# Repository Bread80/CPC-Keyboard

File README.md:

# Keyboard for Amstrad CPC Computers

This project is a keyboard suitable for direct connection to an Amstrad CPC. The PCB uses tactile switches which can easily be labelled with suitable legends for the keytops. The current layout is that of an Amstrad CPC6128, but the key matrix is the same across all machines. The only differences are in the connector types and pinouts.

This board has connectors which are compatible with:
* CPC464 with PCB keyboard (1x20 pin connector)
* CPC464 with membrane keyboard (2x10 pin connectors)
* CPC664 (1x20 pin connector) **Untested**
* CPC6128 (2x10 pin connectors)

Plus machines: I'm not clear whether they use the same keyboard pinout or not. As such I can't say whether this board works with them or not.

Sadly it's not practical to add mounting holes suitable for mounting the keyboard on top of the CPC mainboard.

The repository includes an SVG file with key legend. This is suitable for the open source [Inkscape](https://inkscape.org) software

## BoM

74x Key switches[1]: Alps Apline SKHCBEA010. Mouser no: 688-SKHCBEA010
74x Keytops + Keycaps[2][3]: Alps Alpine SK2AA00090. Mouser: 688-SK2AA00090
'Standard pin header' (2.54mm spacing)[4]
2x Shunts[4]
Connector(s) (to keyboard)[5]
Connector(s) (to CPC)[6]
Cable (keyboard to CPC)[7]
5x Standoffs, short)[8]: 13mm length, M3 x 0.5, 4.5mm OD, female/female. Mouser: M1260-3005-SS
5x Standoffs, long)[8]: 25mm, M3 x 0.5, 4.5mm OD, female/female. Mouser: 761-M1272-3005-SS
10x Screws[8]: M3 x 6mm. Mouser: 534-9191-3
--also-- key legend (printout)[9]

### Notes:
Mouser codes can be used at http://mouser.com
[1] PCB will accept any generic 12mm 'tactile switch'. The specified model allows a keytop + keycap to be attched. This enables a printed key legend to be used. The same design is available engineered for 'operating force' values. In my tests this model had the best feel.
[2] Other colours are available (for the keytops), product codes SK2AA000x0 where x is 6,7,8,9 (NOTE: other digits are different products!).
[3] This product code includes both keycap and keytop. These are also available separately, but the combined pack is slightly cheaper.
Consult the keyswitch data sheet for the full list of available options: https://www.mouser.co.uk/datasheet/2/15/SKHC-1370786.pdf

[4] For configuration jumpers. Source from ebay etc for sensible pricing. If you don't intend to change settings you can solder an offcut of wire instead.
[5] Unless you need to attach multiple machines your best option here is to directly solder wire to the board. Otherwise pin header is probably the most convenient. You'll either need 1x20 or 2x10 depending on the machine, plus 
[6] Options here depend on your machine. The 20-pin inline connect machines will accept 'Dupont' style connectors, pin header etc. The 2x10 matrix connectors are more of a pin. I've successfully used FPC/FFC cable. With some patience this can be persuaded into the connector. These cables only seem to be available in very short lengths but ribbon (etc) cable can be soldered to the other end to run to the keyboard. Obviously some insulation will be helpful on the joins to prevent it shorting against anything (or each other)! You'll need 2x 10-pin cables, 571-FSN-21A-10 is a suitable Mouser product code.
[7] Discreet cables or a length or ribbon cable is up to you. Not every line is connected but using a 20pin or 2x 10-pin ribbon cable saves you having to etsablish which aren't needed. Cable length is up to you but anything too short will make it difficult to position the keyboard where you want it. I'd suggest a /minimum/ of about eight inches (40cm).
[8] I use standoffs as feet to lift to board of the desk and give space for the wiring underneath. You can give the keyboard some 'raking' by using longer ones at the rear. another option is to use a male/female standoff as an extender. The board is engineered for M3 screws/threads. Note: The PCB has three rows of mounting holes but the central row has not proved necessary and I'll remove them if I do an update. Just use the top and bottom rows.
[9] Provided as an SVG suitable for Inkscape) in this here repository. If creating your own key legend, each key needs to be a maximum 10mm x 10mm

## Known Issues

* The keyswitches have a pair of small lugs on the underside. Fitting them would be easier if the board had siutable holes for them. As is it just needs some care to ensure each switch sits flag and true.

## Assembly guide

### Soldering:
* Pin header. Solder the pin header strips for the settings jumpers. Pin header can easily be snapped into short sections as needed.
* Start with the keyswitches. Mount them any way which fits the holes and you'll be okay! Note that there are small lugs on the underside which make them want to sit at an angle. I /strongly/ recommend taking some care to check they are sitting flat and level. My method is to solder a single leg on each, then inspect and rework as needed to level them. Once they're level solder the remaining pins.
* Connectors. Solder your preference of connector(s), or wire, to the rear of the board. The required connectors are as follows:
For a CPC464 with PCB keyboard: connector J1 (1x20 pin)
For a CPC464 with matrix keyboard: connectors J2 and J3 (2 of 1x10 pin)
For a CPC664: connector J4 (1x20 pin)
For a CPC6128: connectors J2 and J3 (2 of 1x10 pin)

### Keycaps:
* Print out the key legend sheet and cut up. Cutting as accurately to the lines as possible will be beneficial. If you have them available, using a cutting board, craft knife, and steel ruler will probably give a better finish than scissors.
* Before assembling the key top + key legend + key cap consult the assembly diagram at the bottom of page three of the datasheet: https://www.mouser.co.uk/datasheet/2/15/SKHC-1370786.pdf Note the recommended orientation of keytop to keycap and plan which way you'll need to assemble things so your legend ends up the correct way around!
* With the keycap (clear plastic piece) face down on the bench, insert the key legend (paper) face down. Then insert the keytop into the keycap, taking note of the corrent orientation with respect to the key legend.
* Attach the keytop/keycaps to the keyswitches.

### Configuration and Connection

All the connectors are orientated in the same way as those on the Amstrad motherboard. I.e. the pin(s) towards the top of rear of the keyboard PCB are those towards the rear of the motherboard PCB and, for the the dual 10-pin connectors, the right-most connector on the keyboard PCB (when viewed from the top) connects to the right-most connector on the motherboard PCB.

Configuration is *only* needed if using the pair of 10-pin connectors to connect to the motherboard. If connecting to a CPC464, short (with a 'shunt') JP2 and the left-most two pins of JP1. If connecting to a CPC6128 short JP3 and the two right-most pins of JP1. Note that when connecting to a CPC464 JP3 should be left open, when connecting to a CPC6128 JP2 should be left open.

## Keyboard legend file(s)

Keyboard legend files are in the 'legend' folder. The following designs/layouts are available. SVG files can be created, edited and printed with the open source Inkscape software. If you create anything new/interesting please contribute it back to the repository.

UK-CPC6128-with-464-colours.svg - Amstrad CPC6128 layout with UK legend using the colour scheme of an original Amstrad CPC464.

## Licence

My aim with this project is to share something potentially useful with the community but I don't want to see my work being exploited for profit.

Therefore, it's okay to have a board manufactured for your own use and sell off the spare boards for an amount to cover your costs and postage. If you want to sell boards, or derivatives, for profit or as part of a business then talk to me first.

## Contact

Website: https://bread80.com
Github: https://github.com/Bread80
Mastodon: https://mstdn.social/@bread80
Twitter: https://twitter.com/bread80com

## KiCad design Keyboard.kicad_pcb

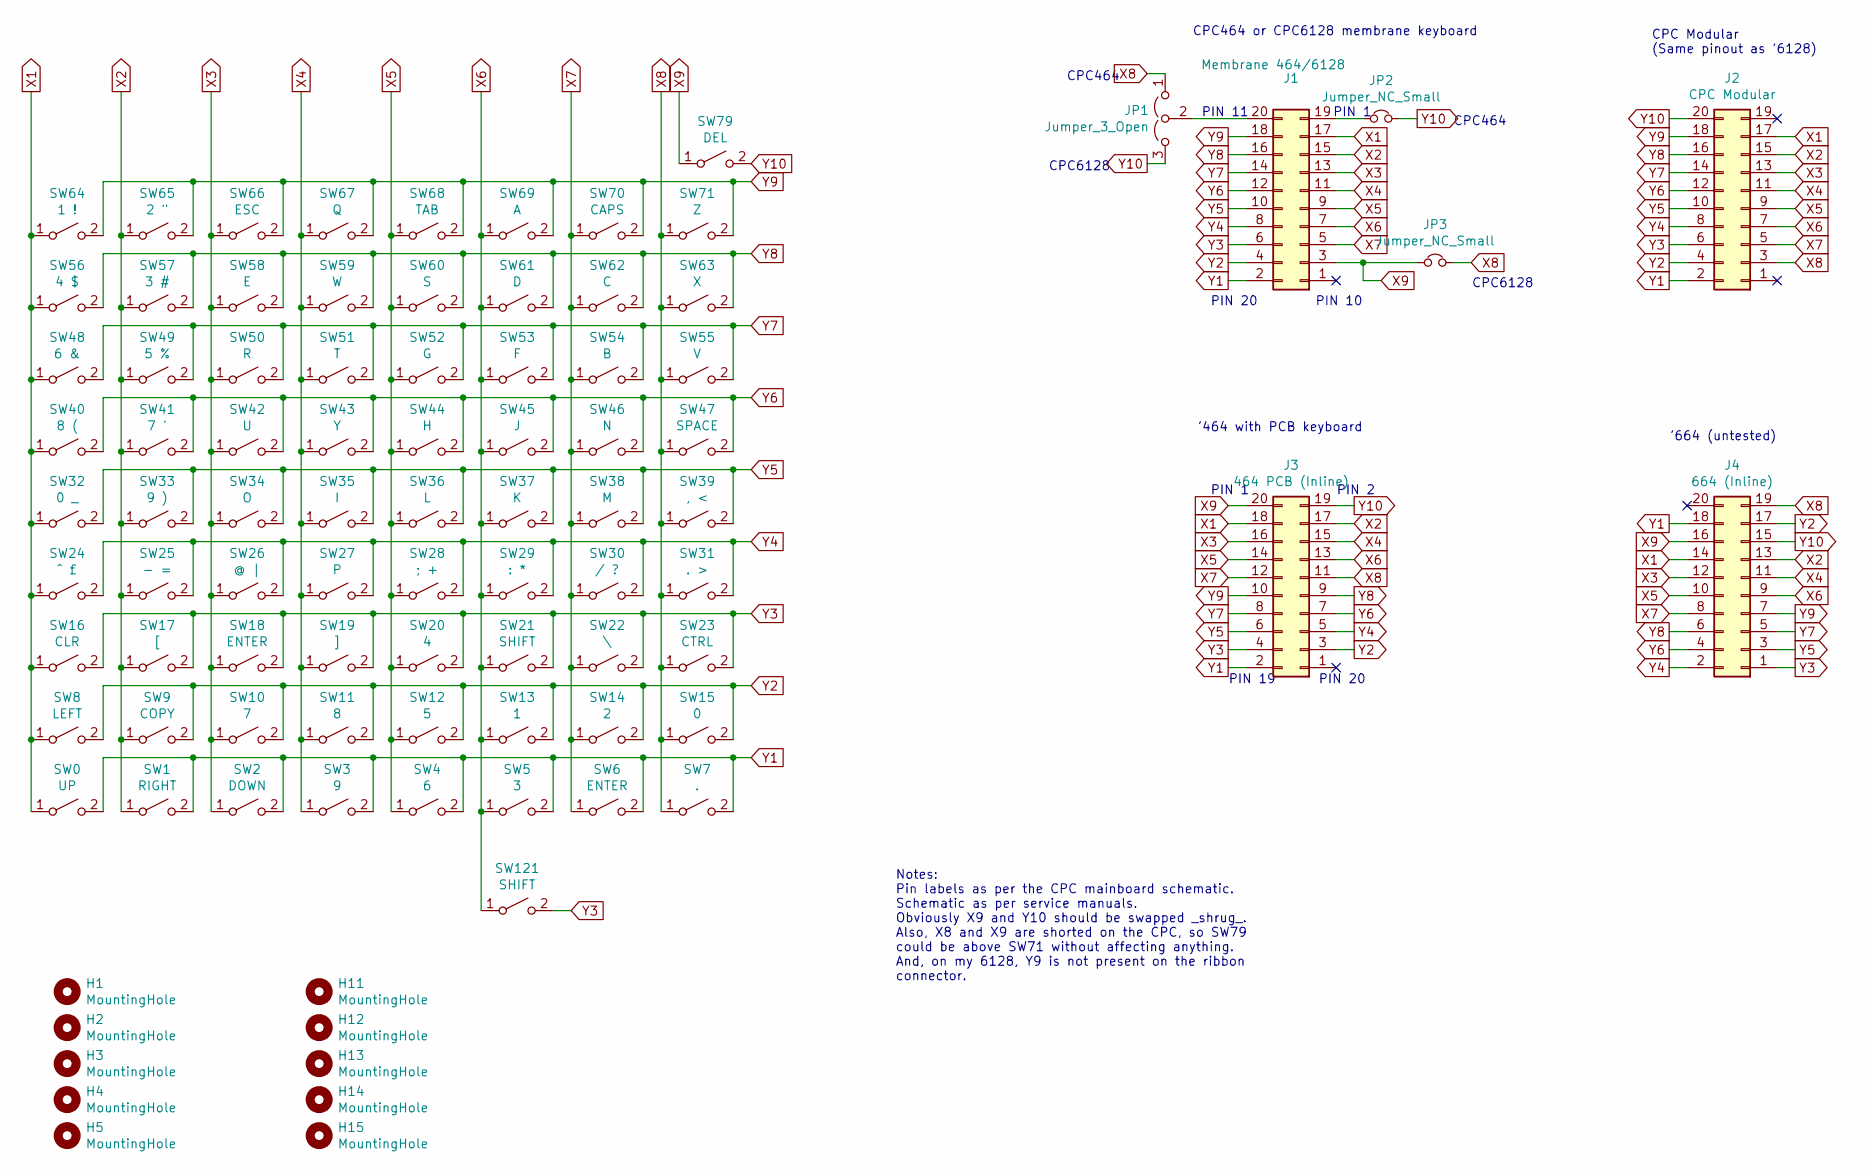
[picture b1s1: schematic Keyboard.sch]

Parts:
H1, H2, H3, H4, H5, H11, H12, H13, H14, H15: MountingHole; MountingHole_3.2mm_M3_DIN965
J1: Membrane 464/6128; IDC-Header_2x10_P2.54mm_Vertical
J2: CPC Modular; IDC-Header_2x10_P2.54mm_Vertical
J3: 464 PCB (Inline); IDC-Header_2x10_P2.54mm_Vertical
J4: 664 (Inline); IDC-Header_2x10_P2.54mm_Vertical
JP1: Jumper_3_Open; PinHeader_1x03_P2.54mm_Vertical
JP2, JP3: Jumper_NC_Small; PinHeader_1x02_P2.54mm_Vertical
SW0: UP; SKHCBEA010
SW1: RIGHT; SKHCBEA010
SW2: DOWN; SKHCBEA010
SW3: 9; SKHCBEA010
SW4: 6; SKHCBEA010
SW5: 3; SKHCBEA010
SW6, SW18: ENTER; SKHCBEA010
SW7: .; SKHCBEA010
SW8: LEFT; SKHCBEA010
SW9: COPY; SKHCBEA010
SW10: 7; SKHCBEA010
SW11: 8; SKHCBEA010
SW12: 5; SKHCBEA010
SW13: 1; SKHCBEA010
SW14: 2; SKHCBEA010
SW15: 0; SKHCBEA010
SW16: CLR; SKHCBEA010
SW17: [; SKHCBEA010
SW19: ]; SKHCBEA010
SW20: 4; SKHCBEA010
SW21, SW121: SHIFT; SKHCBEA010
SW22: \\; SKHCBEA010
SW23: CTRL; SKHCBEA010
SW24: ^ £; SKHCBEA010
SW25: - =; SKHCBEA010
SW26: @ |; SKHCBEA010
SW27: P; SKHCBEA010
SW28: ; +; SKHCBEA010
SW29: : *; SKHCBEA010
SW30: / ?; SKHCBEA010
SW31: . >; SKHCBEA010
SW32: 0 _; SKHCBEA010
SW33: 9 ); SKHCBEA010
SW34: O; SKHCBEA010
SW35: I; SKHCBEA010
SW36: L; SKHCBEA010
SW37: K; SKHCBEA010
SW38: M; SKHCBEA010
SW39: , <; SKHCBEA010
SW40: 8 (; SKHCBEA010
SW41: 7 '; SKHCBEA010
SW42: U; SKHCBEA010
SW43: Y; SKHCBEA010
SW44: H; SKHCBEA010
SW45: J; SKHCBEA010
SW46: N; SKHCBEA010
SW47: SPACE; SKHCBEA010
SW48: 6 &; SKHCBEA010
SW49: 5 %; SKHCBEA010
SW50: R; SKHCBEA010
SW51: T; SKHCBEA010
SW52: G; SKHCBEA010
SW53: F; SKHCBEA010
SW54: B; SKHCBEA010
SW55: V; SKHCBEA010
SW56: 4 $; SKHCBEA010
SW57: 3 #; SKHCBEA010
SW58: E; SKHCBEA010
SW59: W; SKHCBEA010
SW60: S; SKHCBEA010
SW61: D; SKHCBEA010
SW62: C; SKHCBEA010
SW63: X; SKHCBEA010
SW64: 1 !; SKHCBEA010
SW65: 2 \"; SKHCBEA010
SW66: ESC; SKHCBEA010
SW67: Q; SKHCBEA010
SW68: TAB; SKHCBEA010
SW69: A; SKHCBEA010
SW70: CAPS; SKHCBEA010
SW71: Z; SKHCBEA010
SW79: DEL; SKHCBEA010

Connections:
unnamed: J1.19, JP2.2
unnamed: J1.20, JP1.2 (C)
X1: J1.17, J2.17, J3.18, J4.14, SW0.1 (A), SW8.1 (A), SW16.1 (A), SW24.1 (A), SW32.1 (A), SW40.1 (A), SW48.1 (A), SW56.1 (A), SW64.1 (A)
X2: J1.15, J2.15, J3.17, J4.13, SW1.1 (A), SW9.1 (A), SW17.1 (A), SW25.1 (A), SW33.1 (A), SW41.1 (A), SW49.1 (A), SW57.1 (A), SW65.1 (A)
X3: J1.13, J2.13, J3.16, J4.12, SW2.1 (A), SW10.1 (A), SW18.1 (A), SW26.1 (A), SW34.1 (A), SW42.1 (A), SW50.1 (A), SW58.1 (A), SW66.1 (A)
X4: J1.11, J2.11, J3.15, J4.11, SW3.1 (A), SW11.1 (A), SW19.1 (A), SW27.1 (A), SW35.1 (A), SW43.1 (A), SW51.1 (A), SW59.1 (A), SW67.1 (A)
X5: J1.9, J2.9, J3.14, J4.10, SW4.1 (A), SW12.1 (A), SW20.1 (A), SW28.1 (A), SW36.1 (A), SW44.1 (A), SW52.1 (A), SW60.1 (A), SW68.1 (A)
X6: J1.7, J2.7, J3.13, J4.9, SW5.1 (A), SW13.1 (A), SW21.1 (A), SW29.1 (A), SW37.1 (A), SW45.1 (A), SW53.1 (A), SW61.1 (A), SW69.1 (A), SW121.1 (A)
X7: J1.5, J2.5, J3.12, J4.8, SW6.1 (A), SW14.1 (A), SW22.1 (A), SW30.1 (A), SW38.1 (A), SW46.1 (A), SW54.1 (A), SW62.1 (A), SW70.1 (A)
X8: J2.3, J3.11, J4.19, JP1.1 (A), JP3.1, SW7.1 (A), SW15.1 (A), SW23.1 (A), SW31.1 (A), SW39.1 (A), SW47.1 (A), SW55.1 (A), SW63.1 (A), SW71.1 (A)
X9: J1.3, J3.20, J4.16, JP3.2, SW79.1 (A)
Y1: J1.2, J2.2, J3.2, J4.18, SW0.2 (B), SW1.2 (B), SW2.2 (B), SW3.2 (B), SW4.2 (B), SW5.2 (B), SW6.2 (B), SW7.2 (B)
Y2: J1.4, J2.4, J3.3, J4.17, SW8.2 (B), SW9.2 (B), SW10.2 (B), SW11.2 (B), SW12.2 (B), SW13.2 (B), SW14.2 (B), SW15.2 (B)
Y3: J1.6, J2.6, J3.4, J4.1, SW16.2 (B), SW17.2 (B), SW18.2 (B), SW19.2 (B), SW20.2 (B), SW21.2 (B), SW22.2 (B), SW23.2 (B), SW121.2 (B)
Y4: J1.8, J2.8, J3.5, J4.2, SW24.2 (B), SW25.2 (B), SW26.2 (B), SW27.2 (B), SW28.2 (B), SW29.2 (B), SW30.2 (B), SW31.2 (B)
Y5: J1.10, J2.10, J3.6, J4.3, SW32.2 (B), SW33.2 (B), SW34.2 (B), SW35.2 (B), SW36.2 (B), SW37.2 (B), SW38.2 (B), SW39.2 (B)
Y6: J1.12, J2.12, J3.7, J4.4, SW40.2 (B), SW41.2 (B), SW42.2 (B), SW43.2 (B), SW44.2 (B), SW45.2 (B), SW46.2 (B), SW47.2 (B)
Y7: J1.14, J2.14, J3.8, J4.5, SW48.2 (B), SW49.2 (B), SW50.2 (B), SW51.2 (B), SW52.2 (B), SW53.2 (B), SW54.2 (B), SW55.2 (B)
Y8: J1.16, J2.16, J3.9, J4.6, SW56.2 (B), SW57.2 (B), SW58.2 (B), SW59.2 (B), SW60.2 (B), SW61.2 (B), SW62.2 (B), SW63.2 (B)
Y9: J1.18, J2.18, J3.10, J4.7, SW64.2 (B), SW65.2 (B), SW66.2 (B), SW67.2 (B), SW68.2 (B), SW69.2 (B), SW70.2 (B), SW71.2 (B)
Y10: J2.20, J3.19, J4.15, JP1.3 (B), JP2.1, SW79.2 (B)

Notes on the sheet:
Notes: Pin labels as per the CPC mainboard schematic. Schematic as per service manuals. Obviously X9 and Y10 should be swapped _shrug_. Also, X8 and X9 are shorted on the CPC, so SW79 could be above SW71 without affecting anything. And, on my 6128, Y9 is not present on the ribbon connector.
CPC464 or CPC6128 membrane keyboard
CPC464
CPC6128
PIN 11
PIN 20
PIN 1
PIN 10
CPC Modular (Same pinout as '6128)
'464 with PCB keyboard
'664 (untested)
PIN 19
PIN 2

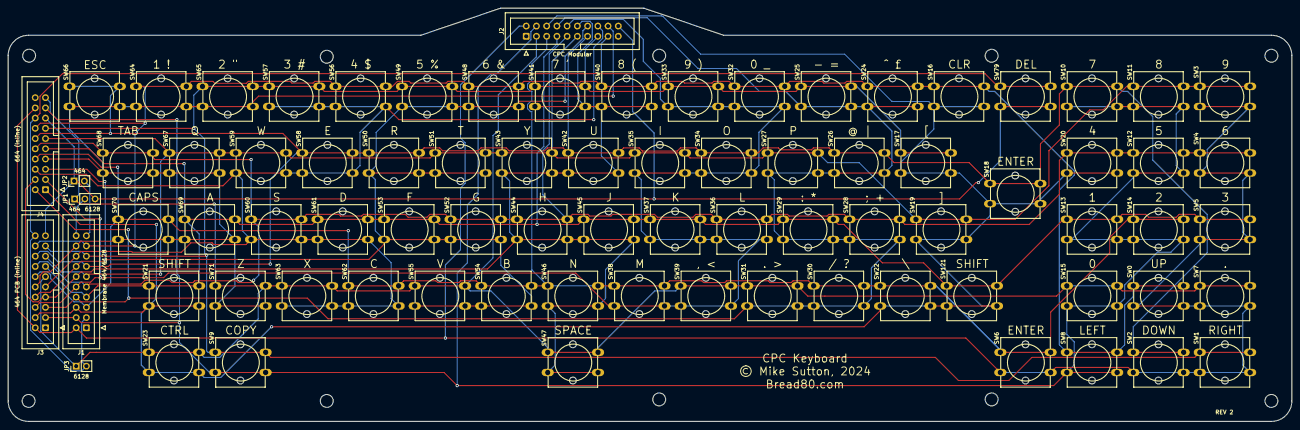
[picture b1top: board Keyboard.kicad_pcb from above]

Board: 2 copper layers, 318.8 x 102.6 mm, 91 parts (0 on the bottom side), 21 nets.

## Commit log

2024-01-19 Added schematic image file

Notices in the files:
Keyboard.kicad_pcb:
© Mike Sutton, 2024
